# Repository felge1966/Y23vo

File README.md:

# Y23vo
Neudesign des Mikrocomputers M.Kramer

Bisher sind folgende Baugruppen realisiert:
- CPU mit RAM und EPROM 
- BWS mit 2K Zeichengenerator 
- Floppycontroller mit u8272 (nach FA 07/1990)
- Grafikdisplaycontroller mit U82720 (nach FA 07/1990)
- 2PIO
- SIO mit U856, U857 und 8251
- Backplane mit 8 Steckplätzen

Alle Baugruppen können mit EFS 29 (A-B oder A-C) Steckverbindern oder alternativ mit DIN 41612 C 2*32 bestückt werden.

Bei CPU, 2PIO und SIO sind GALs als Decoder in Verwendung. 
Die Erstellung erfoolgte mit WinCUPL. Die Sourcen liegen im Verzeichnis

Die Verzeichnisse Redesign 2020 und Redesign 2022 stammen von der Nachetwicklung im Robotrontechnik-Forum.
-> ferrytale

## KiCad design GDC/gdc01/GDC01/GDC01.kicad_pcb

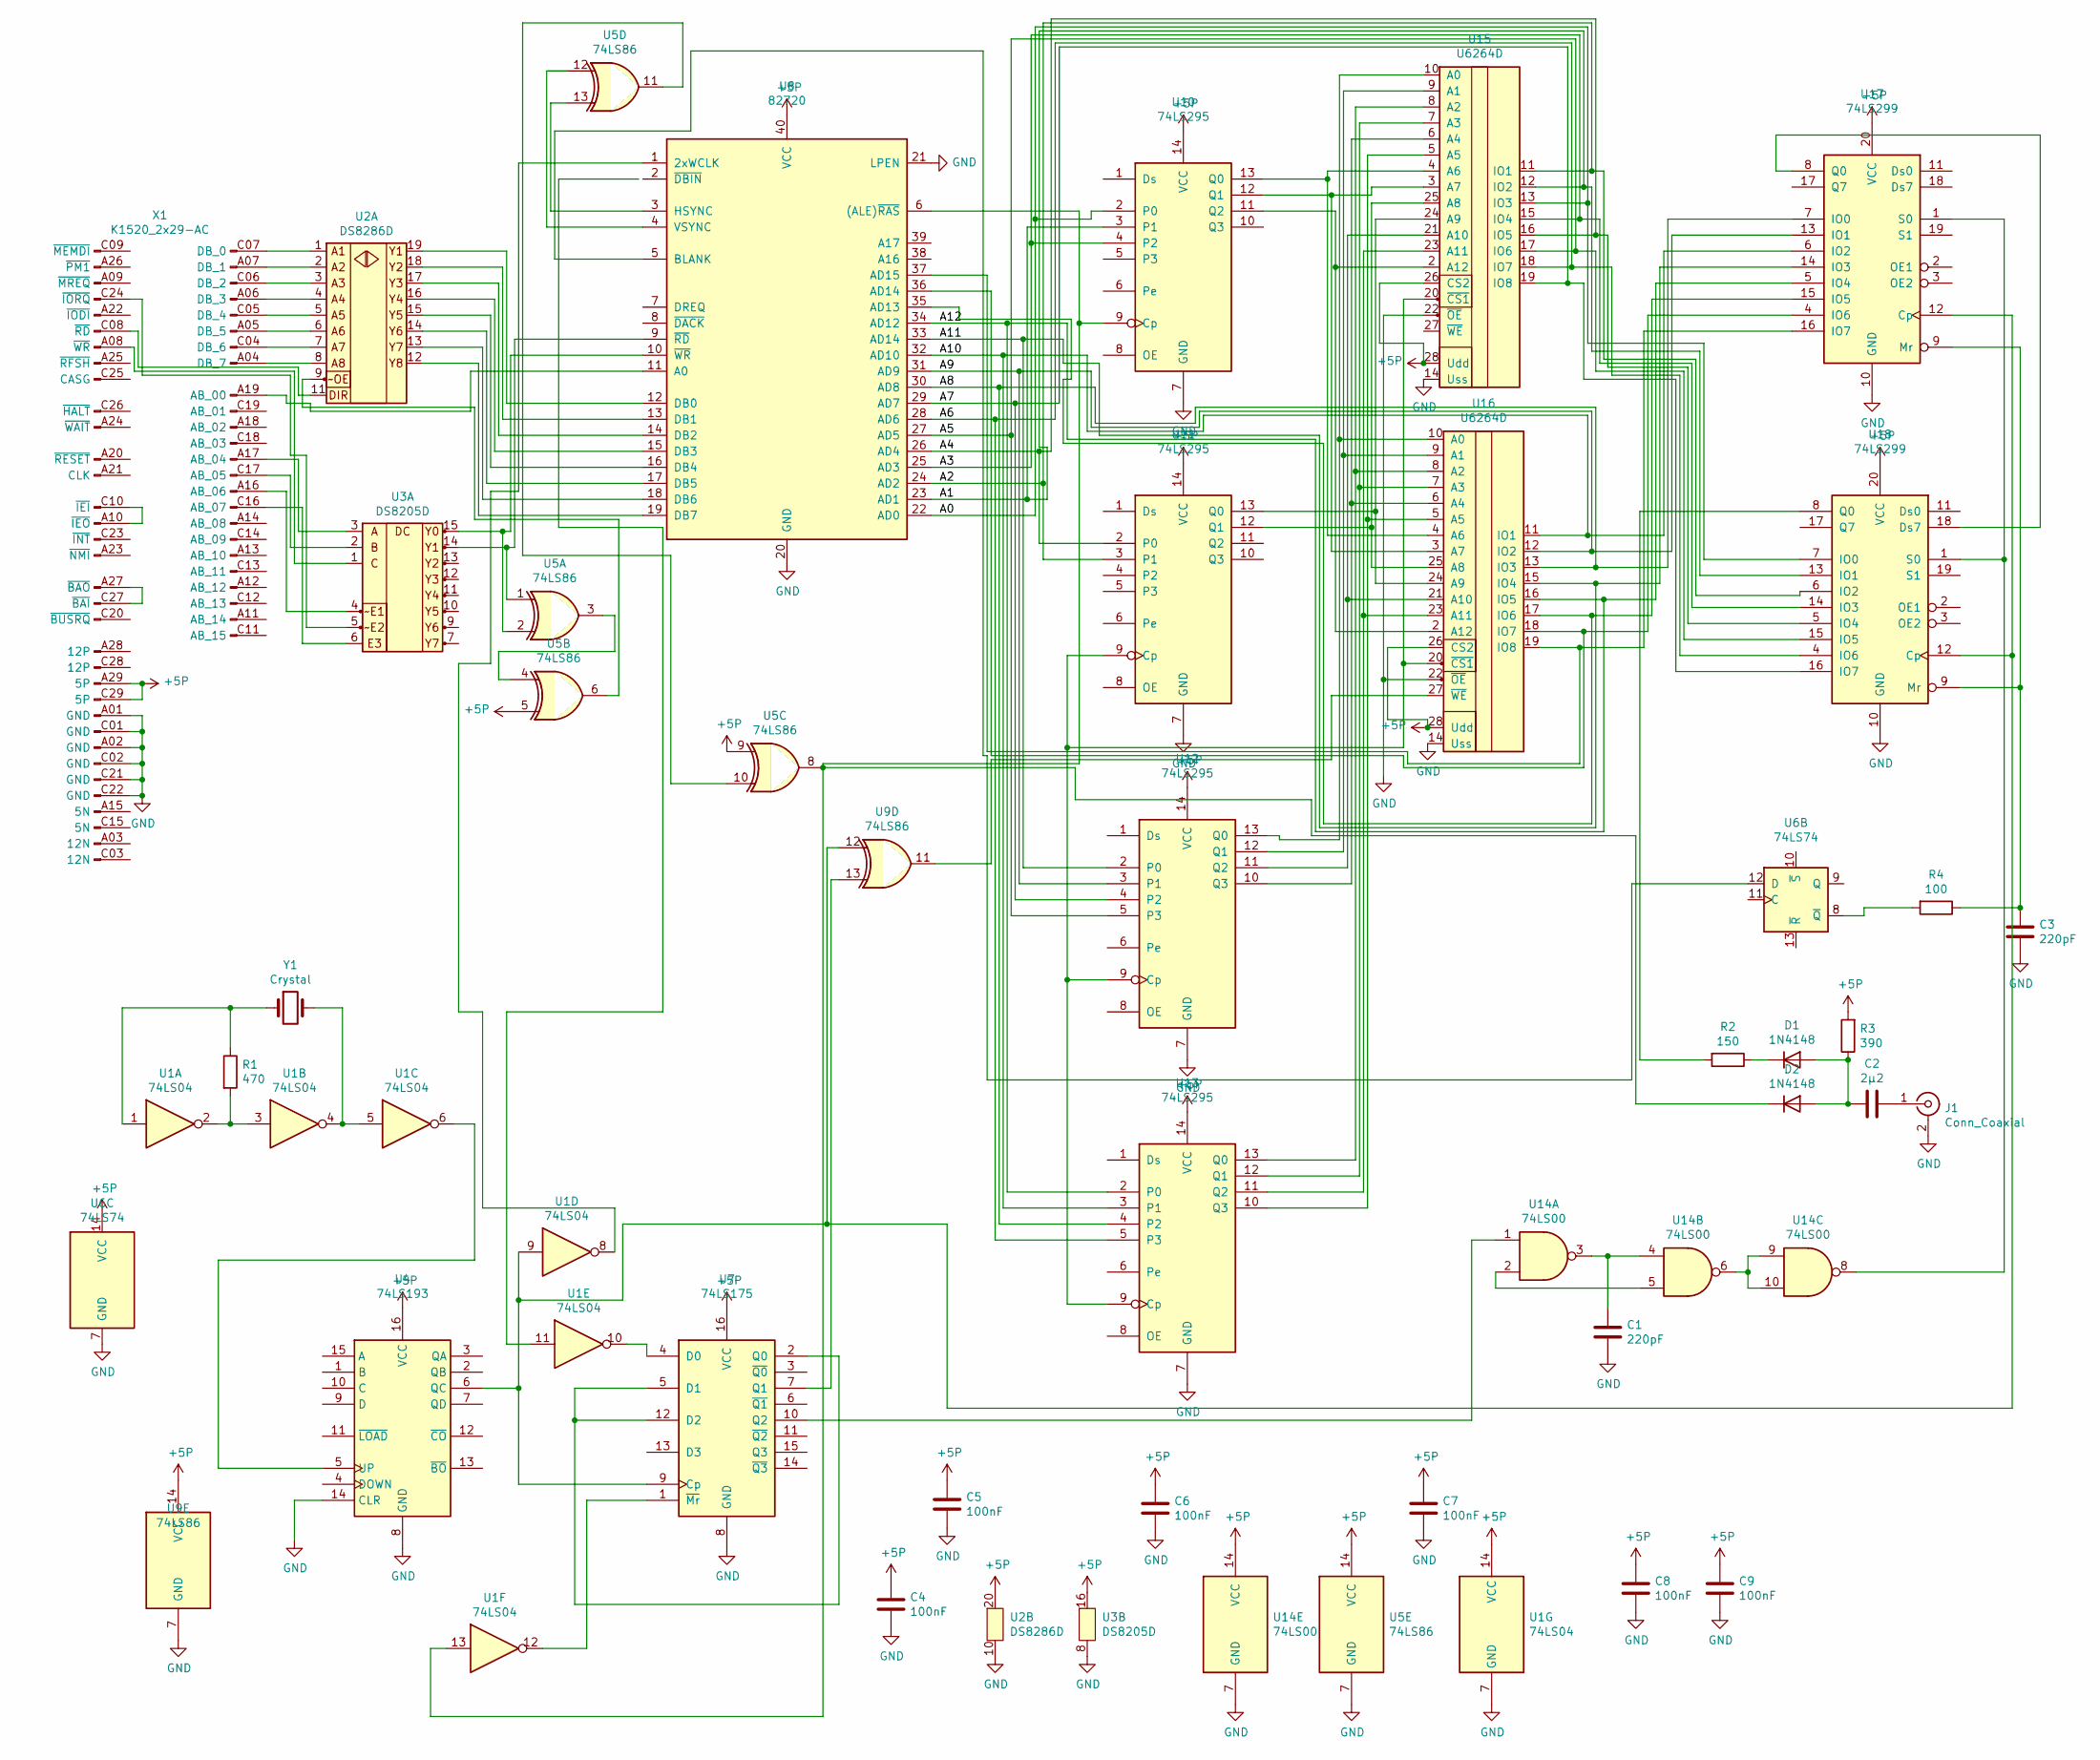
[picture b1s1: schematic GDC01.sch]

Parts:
C1, C3: 220pF; C_Disc_D3.0mm_W1.6mm_P2.50mm
C2: 2µ2; C_Axial_L22.0mm_D9.5mm_P27.50mm_Horizontal
C4, C5, C6, C7, C8, C9: 100nF; C_Disc_D3.0mm_W1.6mm_P2.50mm
D1, D2: 1N4148; D_DO-15_P10.16mm_Horizontal
J1: Conn_Coaxial; chinch
R1: 470; R_Axial_DIN0207_L6.3mm_D2.5mm_P10.16mm_Horizontal
R2: 150; R_Axial_DIN0207_L6.3mm_D2.5mm_P10.16mm_Horizontal
R3: 390; R_Axial_DIN0207_L6.3mm_D2.5mm_P10.16mm_Horizontal
R4: 100; R_Axial_DIN0207_L6.3mm_D2.5mm_P10.16mm_Horizontal
U1: 74LS04; DIP-14_W7.62mm_LongPads
U2: DS8286D; DIP-20_W7.62mm_LongPads
U3: DS8205D; DIP-16_W7.62mm_LongPads
U4: 74LS193; DIP-16_W7.62mm_LongPads
U5, U9: 74LS86; DIP-14_W7.62mm_LongPads
U6: 74LS74; DIP-14_W7.62mm_LongPads
U7: 74LS175; DIP-16_W7.62mm_LongPads
U8: 82720; DIP-40_W15.24mm
U10, U11, U12, U13: 74LS295; DIP-14_W7.62mm_LongPads
U14: 74LS00; DIP-14_W7.62mm_LongPads
U15, U16: U6264D; DIP-28_W15.24mm_LongPads
U17, U18: 74LS299; DIP-20_W7.62mm_LongPads
X1: K1520_2x29-AC; K1520_EFS2x29_DIN_male
Y1: Crystal; Crystal_HC49-U_Vertical

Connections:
+5P: C4.1, C5.1, C6.1, C7.1, C8.1, C9.1, R3.2, U1.14 (VCC), U2.20 (Vcc), U3.16 (Vcc), U4.16 (VCC), U5.5, U5.9, U5.14 (VCC), U6.14 (VCC), U7.16 (VCC), U8.40 (VCC), U9.14 (VCC), U10.14 (VCC), U11.14 (VCC), U12.14 (VCC), U13.14 (VCC), U14.14 (VCC), U15.26 (CS2), U15.28 (Udd), U16.26 (CS2), U16.28 (Udd), U17.20 (VCC), U18.20 (VCC), X1.A29 (5P), X1.C29 (5P)
/A0: U8.22 (AD0), U10.2 (P0), U15.13 (IO3), U18.7 (IO0)
/A1: U8.23 (AD1), U10.3 (P1), U15.12 (IO2), U18.13 (IO1)
/A2: U8.24 (AD2), U11.3 (P1), U15.11 (IO1), U18.6 (IO2)
/A3: U8.25 (AD3), U10.4 (P2), U15.15 (IO4), U18.14 (IO3)
/A4: U8.26 (AD4), U11.2 (P0), U15.16 (IO5), U18.5 (IO4)
/A5: U8.27 (AD5), U12.5 (P3), U15.17 (IO6), U18.15 (IO5)
/A6: U8.28 (AD6), U13.5 (P3), U15.18 (IO7), U18.4 (IO6)
/A7: U8.29 (AD7), U12.4 (P2), U15.19 (IO8), U18.16 (IO7)
/A8: U8.30 (AD8), U13.4 (P2), U16.13 (IO3), U17.7 (IO0)
/A9: U8.31 (AD9), U12.3 (P1), U16.12 (IO2), U17.13 (IO1)
/A10: U8.32 (AD10), U13.3 (P1), U16.11 (IO1), U17.6 (IO2)
/A11: U8.33 (AD14), U12.2 (P0), U16.15 (IO4), U17.14 (IO3)
/A12: U8.34 (AD12), U13.2 (P0), U16.16 (IO5), U17.5 (IO4)
GND: C1.2, C3.2, C4.2, C5.2, C6.2, C7.2, C8.2, C9.2, J1.2 (Ext), U1.7 (GND), U2.10 (GND), U3.8 (GND), U4.8 (GND), U4.14 (CLR), U5.7 (GND), U6.7 (GND), U7.8 (GND), U8.20 (GND), U8.21 (LPEN), U9.7 (GND), U10.7 (GND), U11.7 (GND), U12.7 (GND), U13.7 (GND), U14.7 (GND), U15.14 (Uss), U15.22 (~OE), U16.14 (Uss), U16.22 (~OE), U17.10 (GND), U18.10 (GND), X1.A01 (GND), X1.A02 (GND), X1.C01 (GND), X1.C02 (GND), X1.C21 (GND), X1.C22 (GND)
unnamed: C1.1, U14.3, U14.4
unnamed: C2.1, J1.1 (In)
unnamed: C2.2, D1.2 (A), D2.2 (A), R3.1
unnamed: C3.1, R4.1, U17.9 (Mr), U18.9 (Mr)
unnamed: D1.1 (K), R2.1
unnamed: D2.1 (K), U1.13, U5.8, U8.6 ((ALE)~RAS~), U10.9 (Cp)
unnamed: R1.1, U1.1, Y1.1
unnamed: R1.2, U1.2, U1.3
unnamed: R2.2, U18.8 (Q0)
unnamed: R4.2, U6.8 (~Q)
unnamed: U1.4, U1.5, Y1.2
unnamed: U1.6, U4.5 (UP)
unnamed: U1.8, U8.1 (2xWCLK)
unnamed: U1.9, U4.6 (QC), U7.9 (Cp), U9.12, U17.12 (Cp), U18.12 (Cp)
unnamed: U1.10, U7.4 (D0)
unnamed: U1.12, U7.1 (~Mr)
unnamed: U2.1 (A1), X1.C07 (DB_0)
unnamed: U2.2 (A2), X1.A07 (DB_1)
unnamed: U2.3 (A3), X1.C06 (DB_2)
unnamed: U2.4 (A4), X1.A06 (DB_3)
unnamed: U2.5 (A5), X1.C05 (DB_4)
unnamed: U2.6 (A6), X1.A05 (DB_5)
unnamed: U2.7 (A7), X1.C04 (DB_6)
unnamed: U2.8 (A8), X1.A04 (DB_7)
unnamed: U2.9 (~OE), U5.6
unnamed: U2.11 (STB), X1.C08 (~RD)
unnamed: U2.12 (Y8), U8.19 (DB7)
unnamed: U2.13 (Y7), U8.18 (DB6)
unnamed: U2.14 (Y6), U8.17 (DB5)
unnamed: U2.15 (Y5), U8.16 (DB4)
unnamed: U2.16 (A4), U8.15 (DB3)
unnamed: U2.17 (Y3), U8.14 (DB2)
unnamed: U2.18 (Y2), U8.13 (DB1)
unnamed: U2.19 (Y1), U8.12 (DB0)
unnamed: U3.1 (C), X1.A08 (~WR)
unnamed: U3.2 (B), X1.C17 (AB_05)
unnamed: U3.3 (A), X1.A17 (AB_04)
unnamed: U3.4 (~E1), X1.A16 (AB_06)
unnamed: U3.5 (~E2), X1.C24 (~IORQ)
unnamed: U3.6 (E3), X1.C16 (AB_07)
unnamed: U3.14 (Y1), U5.1, U8.9 (~RD~)
unnamed: U3.15 (Y0), U5.2, U8.10 (~WR~)
unnamed: U5.3, U5.4
unnamed: U5.10, U5.11
unnamed: U5.12, U8.4 (VSYNC)
unnamed: U5.13, U8.3 (HSYNC)
unnamed: U6.12 (D), U8.5 (BLANK)
unnamed: U7.7 (Q1), U9.13
unnamed: U7.2 (Q0), U7.5 (D1), U7.12 (D2)
unnamed: U8.11 (A0), X1.A19 (AB_00)
unnamed: U10.11 (Q2), U15.2 (A12), U16.2 (A12)
unnamed: U10.12 (Q1), U15.3 (A7), U16.3 (A7)
unnamed: U10.13 (Q0), U15.4 (A6), U16.4 (A6)
unnamed: U11.9 (Cp), U12.9 (Cp), U13.9 (Cp), U15.20 (~CS1), U16.20 (~CS1)
unnamed: U11.12 (Q1), U15.25 (A8), U16.25 (A8)
unnamed: U11.13 (Q0), U15.24 (A9), U16.24 (A9)
unnamed: U12.10 (Q3), U15.6 (A4), U16.6 (A4)
unnamed: U12.11 (Q2), U15.21 (A10), U16.21 (A10)
unnamed: U12.12 (Q1), U15.9 (A1), U16.9 (A1)
unnamed: U12.13 (Q0), U15.10 (A0), U16.10 (A0)
unnamed: U13.10 (Q3), U15.5 (A5), U16.5 (A5)
unnamed: U13.11 (Q2), U15.23 (A11), U16.23 (A11)
unnamed: U13.12 (Q1), U15.7 (A3), U16.7 (A3)
unnamed: U13.13 (Q0), U15.8 (A2), U16.8 (A2)
unnamed: U7.10 (Q2), U14.1
unnamed: U14.2, U14.5
unnamed: U14.8, U17.1 (S0), U18.1 (S0)
unnamed: U14.6, U14.9, U14.10
unnamed: U8.35 (AD13), U16.17 (IO6), U17.15 (IO5)
unnamed: U8.36 (AD14), U16.18 (IO7), U17.4 (IO6)
unnamed: U8.37 (AD15), U16.19 (IO8), U17.16 (IO7)
unnamed: U9.11, U16.27 (~WE)
unnamed: U17.8 (Q0), U18.18 (Ds7)
unnamed: X1.A10 (~IEO), X1.C10 (~IEI)
unnamed: X1.A27 (~BAO), X1.C27 (~BAI)

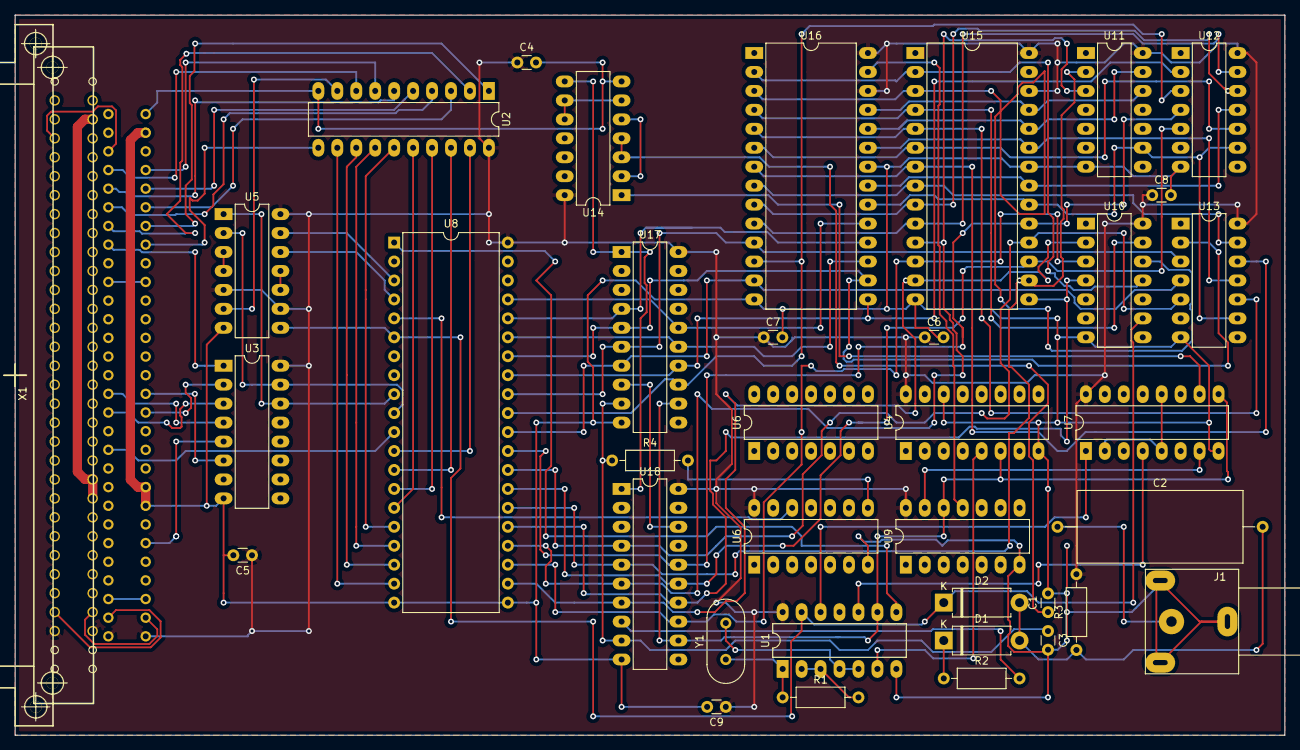
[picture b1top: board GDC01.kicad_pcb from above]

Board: 2 copper layers, 170.2 x 96.5 mm, 37 parts (0 on the bottom side), 90 nets.

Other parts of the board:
U6#2: 74LS74; DIP-14_W7.62mm_LongPads

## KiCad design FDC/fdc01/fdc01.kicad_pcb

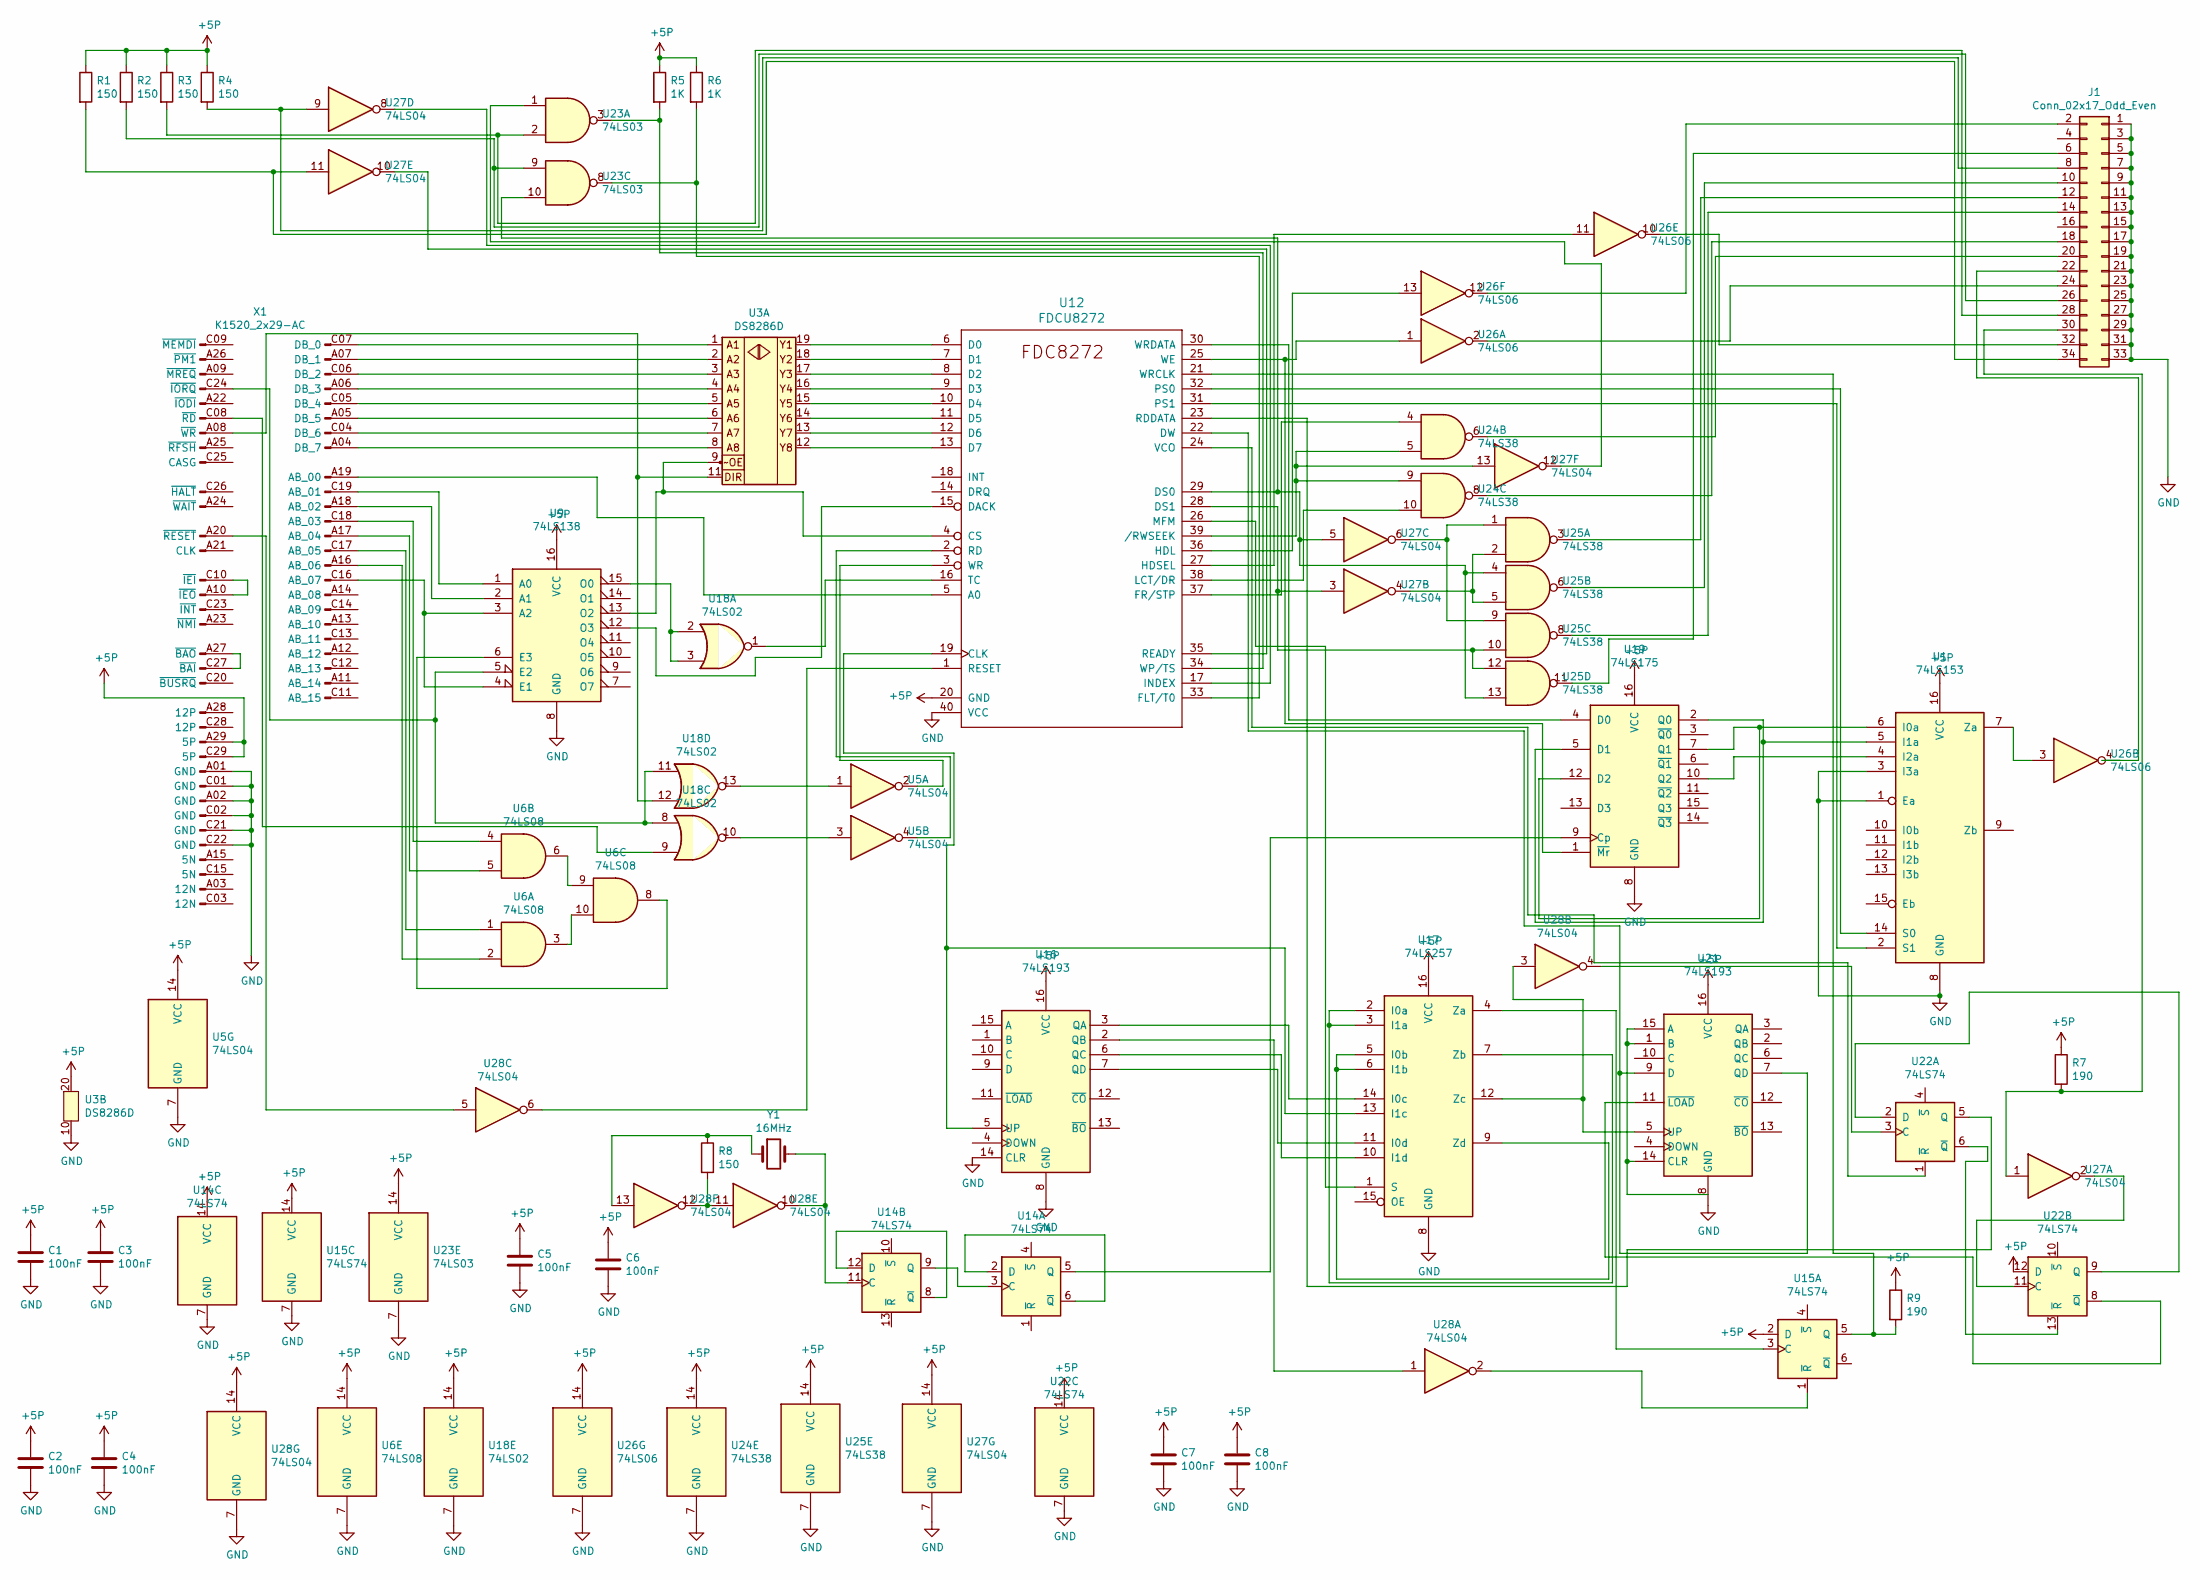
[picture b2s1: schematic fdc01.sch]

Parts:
C1, C2, C3, C4, C5, C6, C7, C8: 100nF; C_Disc_D3.0mm_W2.0mm_P2.50mm
J1: Conn_02x17_Odd_Even; PinSocket_2x17_P2.54mm_Horizontal
R1, R2, R3, R4, R8: 150; R_Axial_DIN0207_L6.3mm_D2.5mm_P10.16mm_Horizontal
R5, R6: 1K; R_Axial_DIN0207_L6.3mm_D2.5mm_P10.16mm_Horizontal
R7, R9: 190; R_Axial_DIN0207_L6.3mm_D2.5mm_P10.16mm_Horizontal
U1: 74LS153; DIP-16_W7.62mm_LongPads
U3: DS8286D; DIP-20_W7.62mm_LongPads
U5, U27, U28: 74LS04; DIP-14_W7.62mm_LongPads
U6: 74LS08; DIP-14_W7.62mm_LongPads
U9: 74LS138; DIP-16_W7.62mm_LongPads
U12: FDCU8272; DIP-40_W15.24mm_LongPads
U14, U15, U22: 74LS74; DIP-14_W7.62mm_LongPads
U16, U21: 74LS193; DIP-16_W7.62mm_LongPads
U17: 74LS257; DIP-16_W7.62mm_LongPads
U18: 74LS02; DIP-14_W7.62mm_LongPads
U19: 74LS175; DIP-16_W7.62mm_LongPads
U23: 74LS03; DIP-14_W7.62mm_LongPads
U24, U25: 74LS38; DIP-14_W7.62mm_LongPads
U26: 74LS06; DIP-14_W7.62mm_LongPads
X1: K1520_2x29-AC; K1520_EFS2x29_DIN_male
Y1: 16MHz; Crystal_HC49-U_Vertical

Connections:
+5P: C1.1, C2.1, C3.1, C4.1, C5.1, C6.1, C7.1, C8.1, R1.1, R2.1, R3.1, R4.1, R5.1, R6.1, R7.1, R9.1, U1.16 (VCC), U3.20 (Vcc), U5.14 (VCC), U6.14 (VCC), U9.16 (VCC), U12.20 (GND), U14.14 (VCC), U15.2 (D), U15.14 (VCC), U16.16 (VCC), U17.16 (VCC), U18.14 (VCC), U19.16 (VCC), U21.16 (VCC), U22.12 (D), U22.14 (VCC), U23.14 (VCC), U24.14 (VCC), U25.14 (VCC), U26.14 (VCC), U27.14 (VCC), U28.14 (VCC), X1.A29 (5P), X1.C29 (5P)
GND: C1.2, C2.2, C3.2, C4.2, C5.2, C6.2, C7.2, C8.2, J1.1, J1.3, J1.5, J1.7, J1.9, J1.11, J1.13, J1.15, J1.17, J1.19, J1.21, J1.23, J1.25, J1.27, J1.29, J1.31, J1.33, U1.1 (Ea), U1.3 (I3a), U1.8 (GND), U3.10 (GND), U5.7 (GND), U6.7 (GND), U9.8 (GND), U12.40 (VCC), U14.7 (GND), U15.7 (GND), U16.8 (GND), U16.14 (CLR), U17.8 (GND), U18.7 (GND), U19.8 (GND), U21.8 (GND), U22.7 (GND), U23.7 (GND), U24.7 (GND), U25.7 (GND), U26.7 (GND), U27.7 (GND), U28.7 (GND), X1.A01 (GND), X1.A02 (GND), X1.C01 (GND), X1.C02 (GND), X1.C21 (GND), X1.C22 (GND)
unnamed: J1.2, U26.12
unnamed: J1.6, U25.11
unnamed: J1.8, R4.2, U27.9
unnamed: J1.10, U25.6
unnamed: J1.12, U25.3
unnamed: J1.14, U25.8
unnamed: J1.18, U24.8
unnamed: J1.20, U24.6
unnamed: J1.24, U26.2
unnamed: J1.26, R2.2, U23.9
unnamed: J1.28, R3.2, U23.2
unnamed: J1.30, R7.2, U27.1
unnamed: J1.32, U26.10
unnamed: J1.34, R1.2, U27.11
unnamed: R5.2, U12.34 (WP/TS), U23.3
unnamed: R6.2, U12.33 (FLT/T0), U23.8
unnamed: R8.1, U28.13, Y1.1
unnamed: R8.2, U28.11, U28.12
unnamed: R9.2, U12.21 (WRCLK), U15.5 (Q)
unnamed: U1.2 (S1), U12.31 (PS1)
unnamed: U1.4 (I2a), U19.10 (Q2)
unnamed: U1.5 (I1a), U19.2 (Q0), U19.5 (D1)
unnamed: U1.6 (I0a), U19.7 (Q1), U19.12 (D2)
unnamed: U1.7 (Za), U26.3
unnamed: U1.14 (S0), U12.32 (PS0)
unnamed: U3.1 (A1), X1.C07 (DB_0)
unnamed: U3.2 (A2), X1.A07 (DB_1)
unnamed: U3.3 (A3), X1.C06 (DB_2)
unnamed: U3.4 (A4), X1.A06 (DB_3)
unnamed: U3.5 (A5), X1.C05 (DB_4)
unnamed: U3.6 (A6), X1.A05 (DB_5)
unnamed: U3.7 (A7), X1.C04 (DB_6)
unnamed: U3.8 (A8), X1.A04 (DB_7)
unnamed: U6.1, X1.C17 (AB_05)
unnamed: U6.2, X1.A16 (AB_06)
unnamed: U6.4, X1.C18 (AB_03)
unnamed: U6.5, X1.A17 (AB_04)
unnamed: U6.6, U6.9
unnamed: U6.8, U9.6 (E3)
unnamed: U6.3, U6.10
unnamed: U9.1 (A0), X1.C19 (AB_01)
unnamed: U9.2 (A1), X1.A18 (AB_02)
unnamed: U9.3 (A2), U9.4 (E1), X1.C16 (AB_07)
unnamed: U12.1 (RESET), U28.6
unnamed: U5.4, U12.2 (RD)
unnamed: U5.2, U12.3 (WR)
unnamed: U3.9 (~OE), U9.13 (O2), U12.4 (CS)
unnamed: U12.5 (A0), X1.A19 (AB_00)
unnamed: U3.19 (Y1), U12.6 (D0)
unnamed: U3.18 (Y2), U12.7 (D1)
unnamed: U3.17 (Y3), U12.8 (D2)
unnamed: U3.16 (A4), U12.9 (D3)
unnamed: U3.15 (Y5), U12.10 (D4)
unnamed: U3.14 (Y6), U12.11 (D5)
unnamed: U3.13 (Y7), U12.12 (D6)
unnamed: U3.12 (Y8), U12.13 (D7)
unnamed: U9.12 (O3), U12.15 (DACK)
unnamed: U12.16 (TC), U18.1
unnamed: U12.17 (INDEX), U27.8
unnamed: U12.19 (CLK), U16.5 (UP), U17.13 (I1c)
unnamed: U12.22 (DW), U21.7 (QD), U21.9 (D)
unnamed: U12.23 (RDDATA), U22.5 (Q)
unnamed: U12.24 (VCO), U22.1 (~R)
unnamed: U12.25 (WE), U19.1 (~Mr), U26.1
unnamed: U12.26 (MFM), U17.1 (S)
unnamed: U12.27 (HDSEL), U26.11
unnamed: U12.28 (DS1), U25.10, U25.12, U27.3
unnamed: U12.29 (DS0), U23.10, U25.4, U25.13, U27.5
unnamed: U12.30 (WRDATA), U19.4 (D0)
unnamed: U12.35 (READY), U27.10
unnamed: U12.36 (HDL), U26.13
unnamed: U12.37 (FR/STP), U24.4
unnamed: U12.38 (LCT/DR), U24.10
unnamed: U12.39 (/RWSEEK), U24.5, U24.9, U27.13
unnamed: U14.2 (D), U14.6 (~Q)
unnamed: U14.3 (C), U14.9 (Q)
unnamed: U14.5 (Q), U19.9 (Cp)
unnamed: U14.11 (C), U28.10, Y1.2
unnamed: U14.8 (~Q), U14.12 (D)
unnamed: U15.1 (~R), U28.2
unnamed: U15.3 (C), U17.4 (Za)
unnamed: U16.2 (QB), U28.1
unnamed: U16.3 (QA), U17.14 (I0c)
unnamed: U16.6 (QC), U17.10 (I1d)
unnamed: U16.7 (QD), U17.11 (I0d)
unnamed: U17.2 (I0a), U17.3 (I1a), U17.7 (Zb)
unnamed: U17.5 (I0b), U17.6 (I1b), U17.9 (Zd)
unnamed: U17.12 (Zc), U21.5 (UP), U28.3
unnamed: U9.15 (O0), U18.2, U18.3
unnamed: U18.9, X1.C08 (~RD)
unnamed: U5.3, U18.10
unnamed: U9.5 (E2), U18.8, U18.11, X1.C24 (~IORQ)
unnamed: U3.11 (STB), U18.12, X1.A08 (~WR)
unnamed: U5.1, U18.13
unnamed: U21.1 (B), U21.14 (CLR), U21.15 (A)
unnamed: U21.11 (~LOAD), U22.8 (~Q)
unnamed: U22.2 (D), U22.9 (Q)
unnamed: U22.3 (C), U28.4
unnamed: U22.11 (C), U27.2
unnamed: U22.6 (~Q), U22.13 (~R)
unnamed: U23.1, U27.12
unnamed: U25.1, U25.9, U27.6
unnamed: U25.2, U25.5, U27.4
unnamed: U28.5, X1.A20 (~RESET)
unnamed: X1.A10 (~IEO), X1.C10 (~IEI)
unnamed: X1.A27 (~BAO), X1.C27 (~BAI)

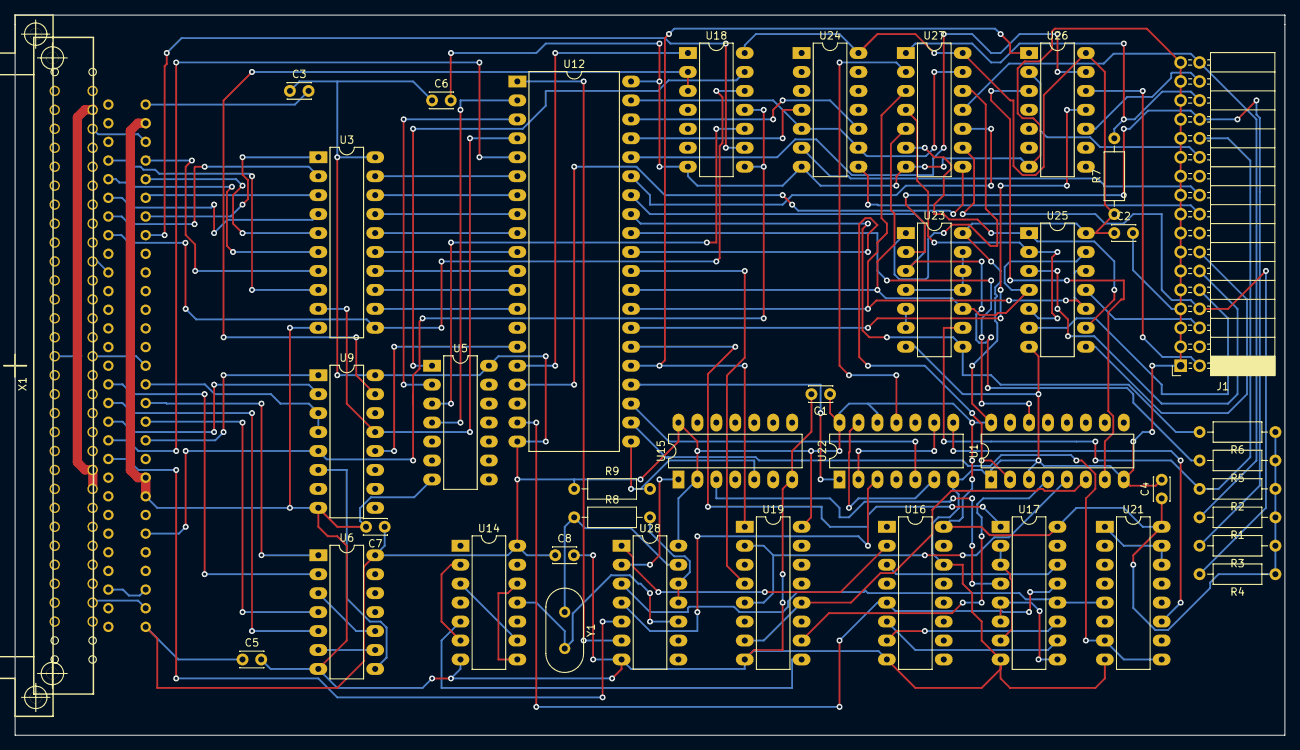
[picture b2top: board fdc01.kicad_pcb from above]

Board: 2 copper layers, 170.2 x 96.5 mm, 40 parts (0 on the bottom side), 108 nets.
